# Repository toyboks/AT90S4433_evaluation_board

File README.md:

# AT90S4433_evaluation_board
Simple board allowing to test codes for AT90S4433 with breadboard circuits.

#22pf for xtal1 xtal2

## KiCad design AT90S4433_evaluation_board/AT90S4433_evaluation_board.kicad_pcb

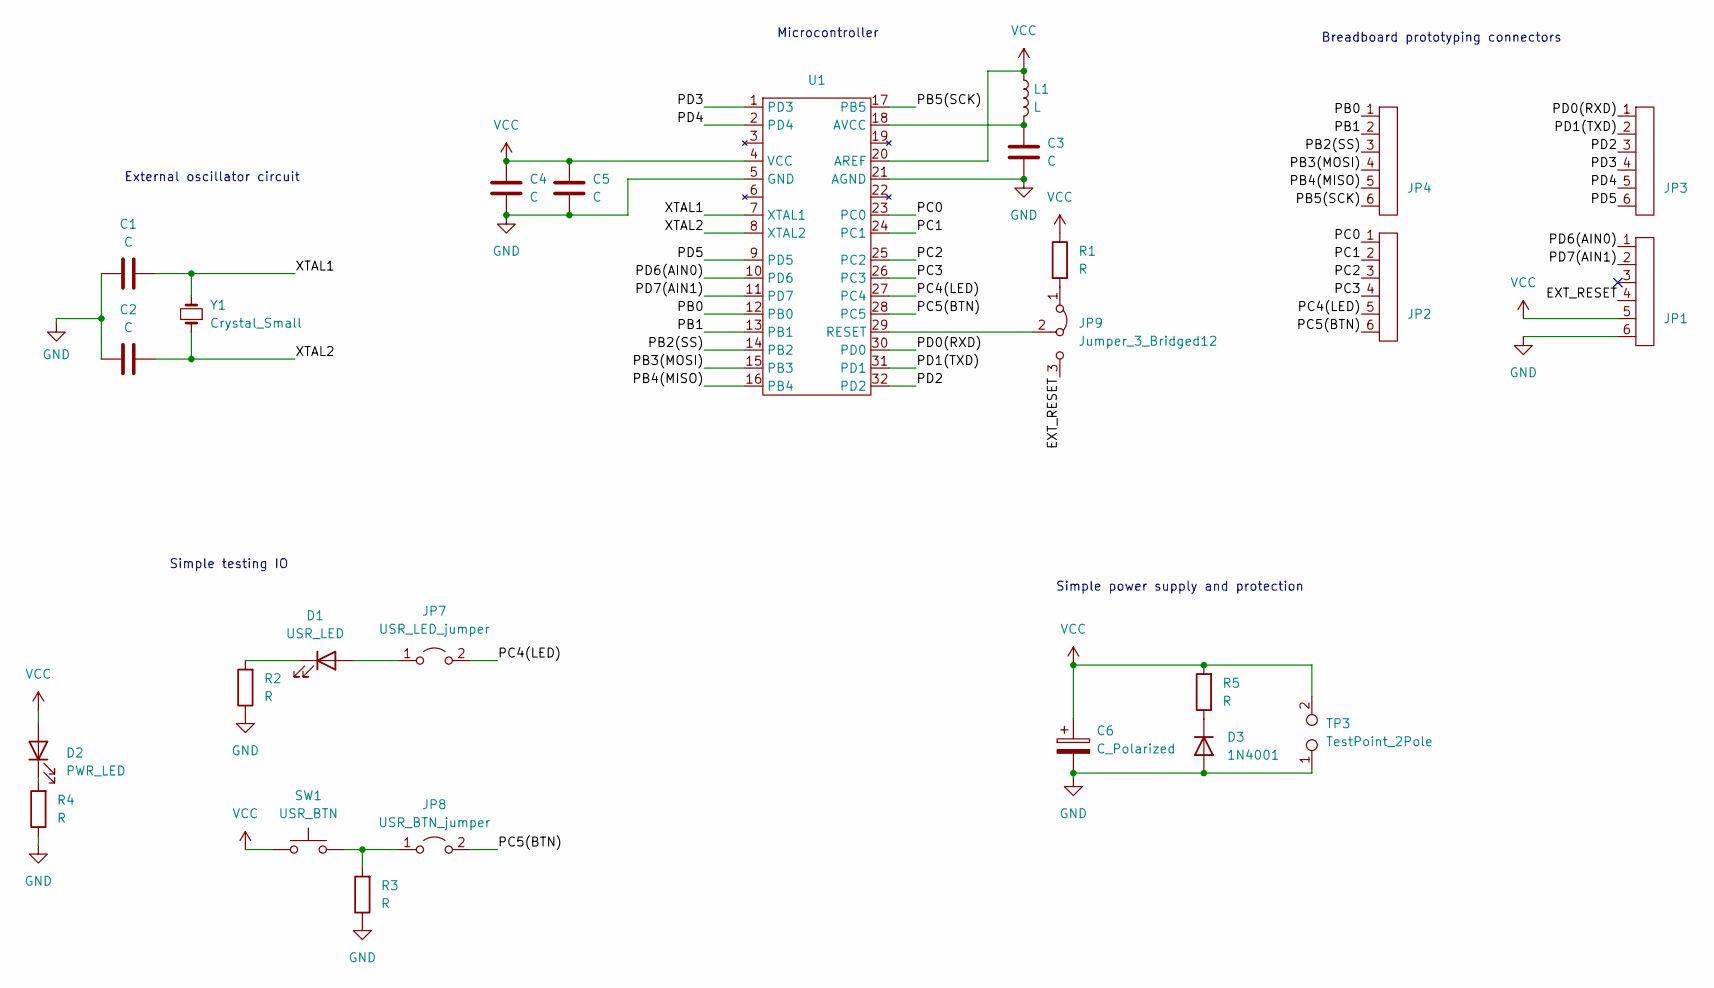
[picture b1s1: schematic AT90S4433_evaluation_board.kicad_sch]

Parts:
C1, C2, C3, C4, C5: C; C_0805_2012Metric
C6: C_Polarized; CP_Radial_D5.0mm_P2.50mm
D1: USR_LED; LED_1206_3216Metric
D2: PWR_LED; LED_1206_3216Metric
D3: 1N4001; D_2512_6332Metric
JP1, JP2, JP3, JP4: breadboard_pins
JP7: USR_LED_jumper; 2_pin_jumper_socket
JP8: USR_BTN_jumper; 2_pin_jumper_socket
JP9: Jumper_3_Bridged12; 3_pin_jumper_socket
L1: L; L_0805_2012Metric
R1, R2, R3, R4, R5: R; R_0805_2012Metric
SW1: USR_BTN; SW_Tactile_Straight_KSA0Axx1LFTR
TP3: TestPoint_2Pole; Power_socket
U1: LQFP-32_7x7mm_P0.8mm
Y1: Crystal_Small; Crystal_HC18-U_Vertical

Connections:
/EXT_RESET: JP1.4, JP9.3 (B)
/PB0: JP4.1, U1.12 (PB0)
/PB1: JP4.2, U1.13 (PB1)
/PB2(SS): JP4.3, U1.14 (PB2)
/PB3(MOSI): JP4.4, U1.15 (PB3)
/PB4(MISO): JP4.5, U1.16 (PB4)
/PB5(SCK): JP4.6, U1.17 (PB5)
/PC0: JP2.1, U1.23 (PC0)
/PC1: JP2.2, U1.24 (PC1)
/PC2: JP2.3, U1.25 (PC2)
/PC3: JP2.4, U1.26 (PC3)
/PC4(LED): JP2.5, JP7.2 (B), U1.27 (PC4)
/PC5(BTN): JP2.6, JP8.2 (B), U1.28 (PC5)
/PD0(RXD): JP3.1, U1.30 (PD0)
/PD1(TXD): JP3.2, U1.31 (PD1)
/PD2: JP3.3, U1.32 (PD2)
/PD3: JP3.4, U1.1 (PD3)
/PD4: JP3.5, U1.2 (PD4)
/PD5: JP3.6, U1.9 (PD5)
/PD6(AIN0): JP1.1, U1.10 (PD6)
/PD7(AIN1): JP1.2, U1.11 (PD7)
/XTAL1: C1.2, U1.7 (XTAL1), Y1.2
/XTAL2: C2.2, U1.8 (XTAL2), Y1.1
GND: C1.1, C2.1, C3.1, C4.1, C5.1, C6.2, D3.2 (A), JP1.6, R2.1, R3.1, R4.1, TP3.1, U1.5 (GND), U1.21 (AGND)
unnamed: D1.2 (A), JP7.1 (A)
unnamed: D1.1 (K), R2.2
unnamed: D2.1 (K), R4.2
unnamed: D3.1 (K), R5.1
unnamed: JP8.1 (A), R3.2, SW1.2
unnamed: JP9.1 (A), R1.2
unnamed: JP9.2 (C), U1.29 (RESET)
unnamed: C3.2, L1.2, U1.18 (AVCC)
VCC: C4.2, C5.2, C6.1, D2.2 (A), JP1.5, L1.1, R1.1, R5.2, SW1.1, TP3.2, U1.4 (VCC), U1.20 (AREF)

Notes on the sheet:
Breadboard prototyping connectors
Simple power supply and protection
Microcontroller
External oscillator circuit
Simple testing IO

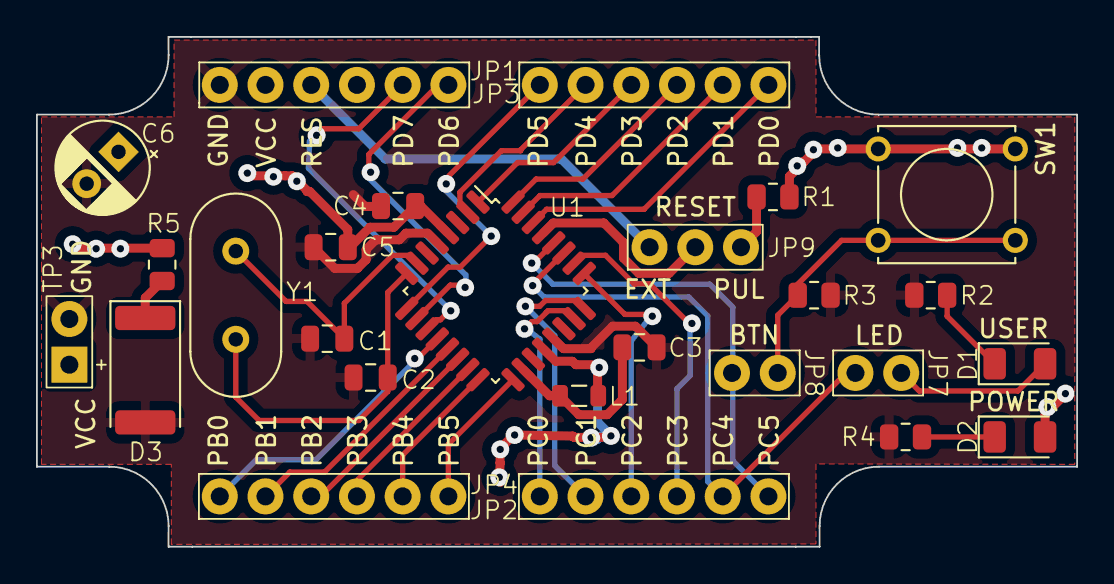
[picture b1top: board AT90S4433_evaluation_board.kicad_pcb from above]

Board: 2 copper layers, 57.8 x 28.3 mm, 26 parts (0 on the bottom side), 33 nets.

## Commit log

2023-09-11 uc lib and initial schematic
2023-09-11 added connectors
2023-09-12 blocking capacitors, test points, external oscillator (schematic)
2023-09-12 pins and uc footprints
2023-09-13 footprints corrections, key components initial layout
2023-09-13 initial footprints for all components, modified layout
2023-09-14 first routes
2023-09-14 completed routing
2023-09-18 corrections
2023-09-18 footprint name changes, vias corrections, description
2023-10-07 pins description fixes
2023-10-07 descriptions, datasheets ignoring
